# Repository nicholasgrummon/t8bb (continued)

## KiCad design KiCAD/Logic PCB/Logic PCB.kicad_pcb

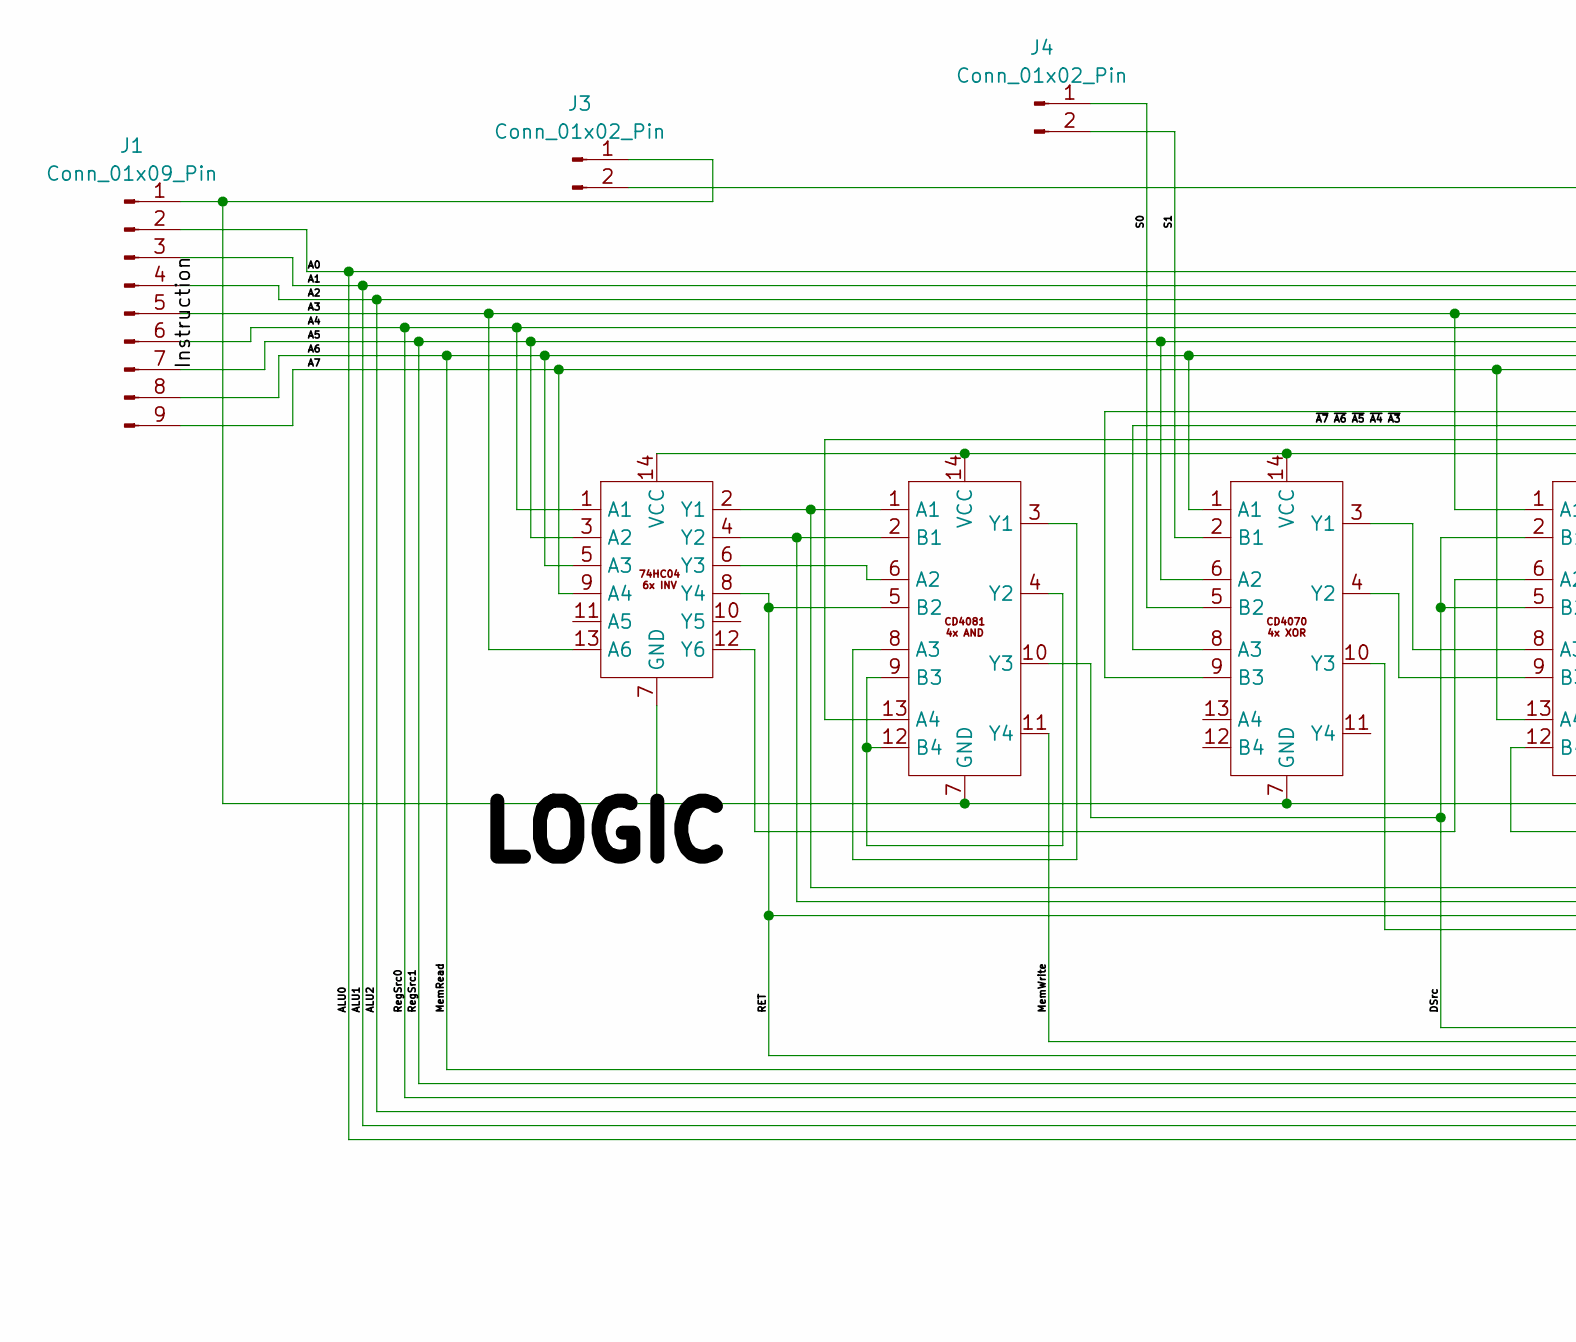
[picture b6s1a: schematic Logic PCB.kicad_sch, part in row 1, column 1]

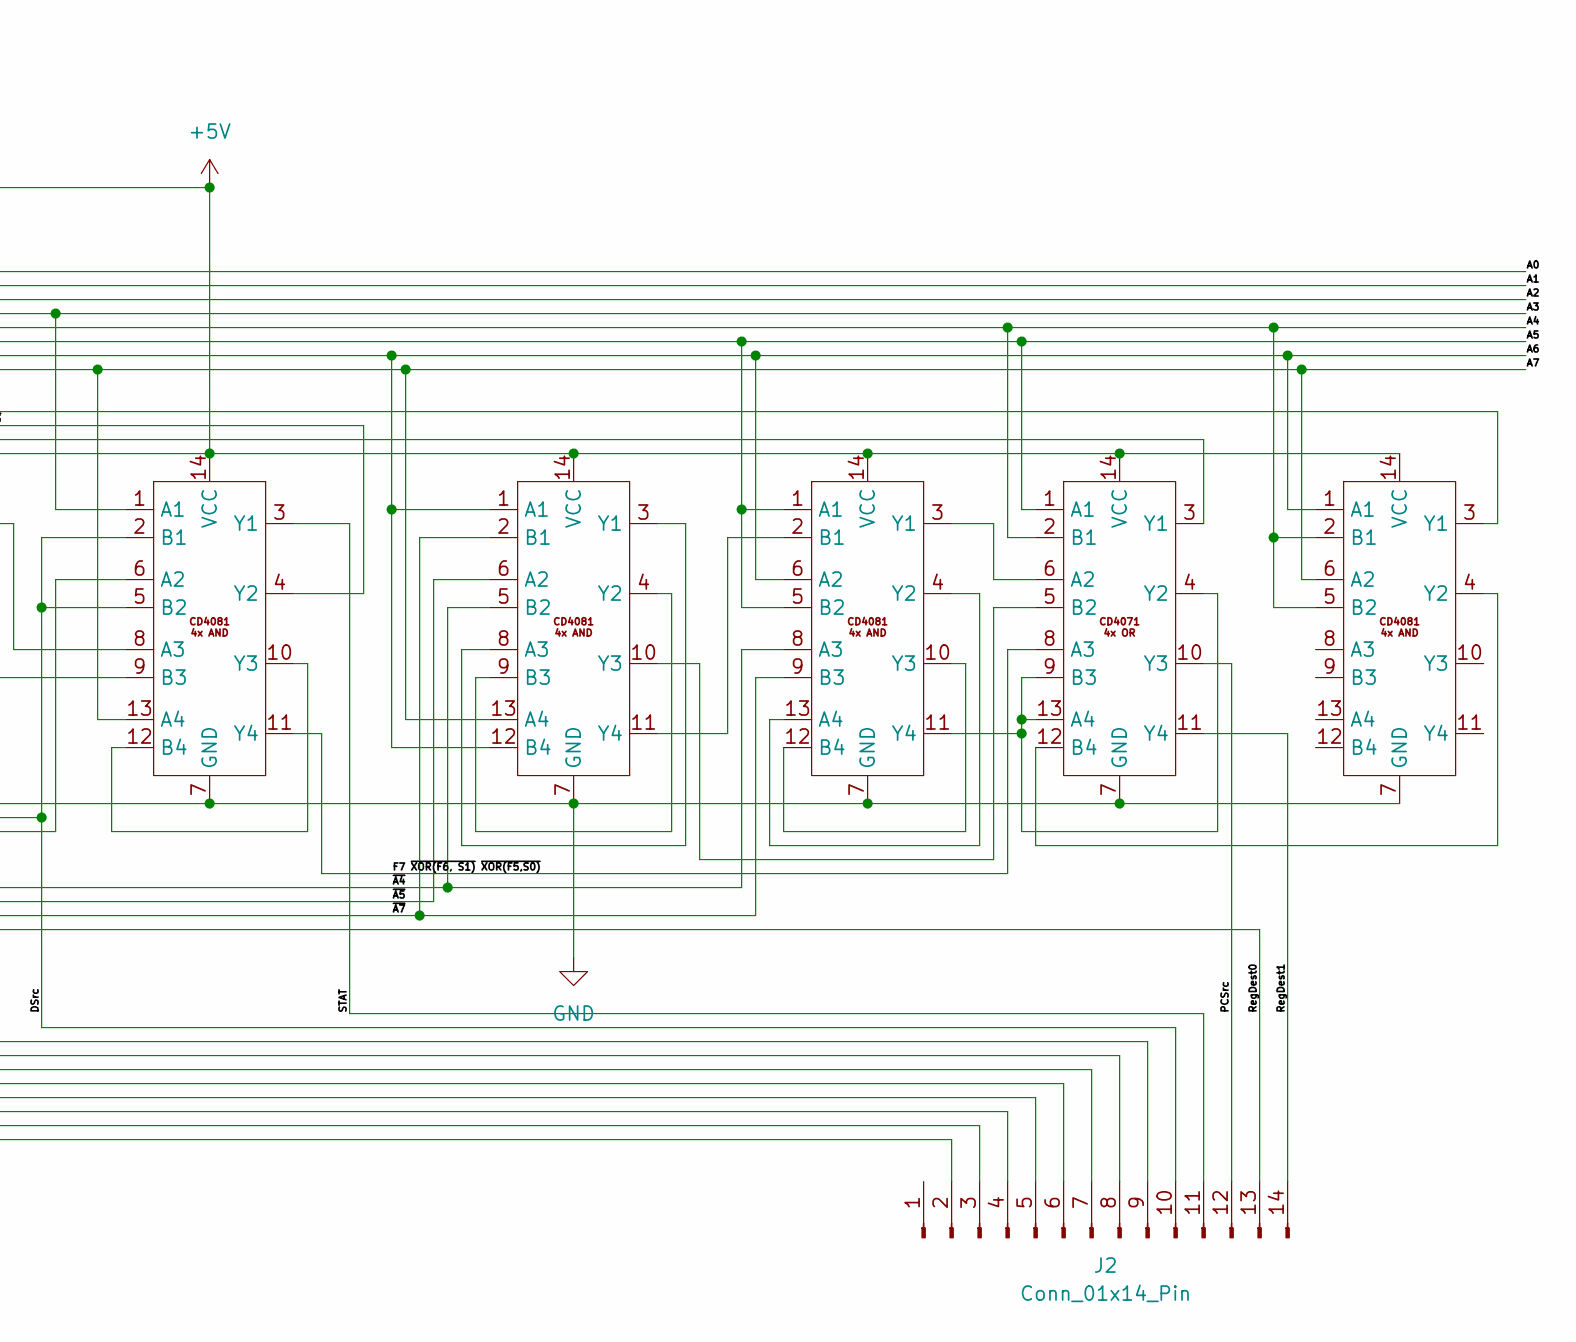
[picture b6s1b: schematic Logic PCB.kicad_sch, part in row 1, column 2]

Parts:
74HC1: 14pinbase; LCSC C507192
CD1, CD3, CD4, CD5, CD7: 14pinbase; LCSC C507156
CD2: 14pinbase; LCSC C30170096
CD6: 14pinbase; LCSC C3007968
J1: Conn_01x09_Pin; PinHeader_1x09_P2.54mm_Vertical
J2: Conn_01x14_Pin; PinHeader_1x14_P2.54mm_Vertical
J3, J4: Conn_01x02_Pin; PinHeader_1x02_P2.54mm_Vertical

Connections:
+5V: 74HC1.14 (VCC), CD1.14 (VCC), CD2.14 (VCC), CD3.14 (VCC), CD4.14 (VCC), CD5.14 (VCC), CD6.14 (VCC), CD7.14 (VCC), J3.2
/A0: J1.2, J2.2
/A1: J1.3, J2.3
/A2: J1.4, J2.4
/A3: 74HC1.13 (A6), CD3.1 (A1), J1.5
/A4: 74HC1.1 (A1), CD6.2 (B1), CD7.2 (B1), CD7.5 (B2), J1.6, J2.5
/A5: 74HC1.3 (A2), CD2.6 (A2), CD5.1 (A1), CD5.5 (B2), CD6.1 (A1), J1.7, J2.6
/A6: 74HC1.5 (A3), CD2.1 (A1), CD4.1 (A1), CD4.12 (B4), CD5.6 (A2), CD7.1 (A1), J1.8, J2.7
/A7: 74HC1.9 (A4), CD3.13 (A4), CD4.13 (A4), CD7.6 (A2), J1.9
/DSrc: CD1.10 (Y3), CD3.2 (B1), CD3.5 (B2), J2.10
/F7 ~XOR(F6, S1) ~XOR(F5,S0): CD3.11 (Y4), CD6.8 (A3)
/MemWrite: CD1.11 (Y4), J2.9
/PCSrc: CD6.10 (Y3), J2.12
/RET: 74HC1.8 (Y4), CD1.5 (B2), CD4.2 (B1), CD5.9 (B3), J2.8
/RegDest0: CD2.10 (Y3), J2.13
/RegDest1: CD6.11 (Y4), J2.14
/S0: CD2.5 (B2), J4.1
/S1: CD2.2 (B1), J4.2
/STAT: CD3.3 (Y1), J2.11
/~A4: 74HC1.2 (Y1), CD1.1 (A1), CD4.5 (B2), CD5.8 (A3)
/~A5: 74HC1.4 (Y2), CD1.2 (B1), CD4.6 (A2)
/~A7 ~A6 ~A5 ~A4 ~A3: CD2.8 (A3), CD3.4 (Y2)
GND: 74HC1.7 (GND), CD1.7 (GND), CD2.7 (GND), CD3.7 (GND), CD4.7 (GND), CD5.7 (GND), CD6.7 (GND), CD7.7 (GND), J1.1, J3.1
unnamed: 74HC1.6 (Y3), CD1.6 (A2)
unnamed: 74HC1.12 (Y6), CD3.6 (A2)
unnamed: CD1.3 (Y1), CD1.8 (A3)
unnamed: CD1.13 (A4), CD6.3 (Y1)
unnamed: CD1.4 (Y2), CD1.9 (B3), CD1.12 (B4)
unnamed: CD2.9 (B3), CD7.3 (Y1)
unnamed: CD2.3 (Y1), CD3.8 (A3)
unnamed: CD2.4 (Y2), CD3.9 (B3)
unnamed: CD3.10 (Y3), CD3.12 (B4)
unnamed: CD4.3 (Y1), CD4.8 (A3)
unnamed: CD4.4 (Y2), CD4.9 (B3)
unnamed: CD4.10 (Y3), CD6.5 (B2)
unnamed: CD4.11 (Y4), CD5.2 (B1)
unnamed: CD5.4 (Y2), CD5.13 (A4)
unnamed: CD5.10 (Y3), CD5.12 (B4)
unnamed: CD5.3 (Y1), CD6.6 (A2)
unnamed: CD5.11 (Y4), CD6.4 (Y2), CD6.9 (B3), CD6.13 (A4)
unnamed: CD6.12 (B4), CD7.4 (Y2)

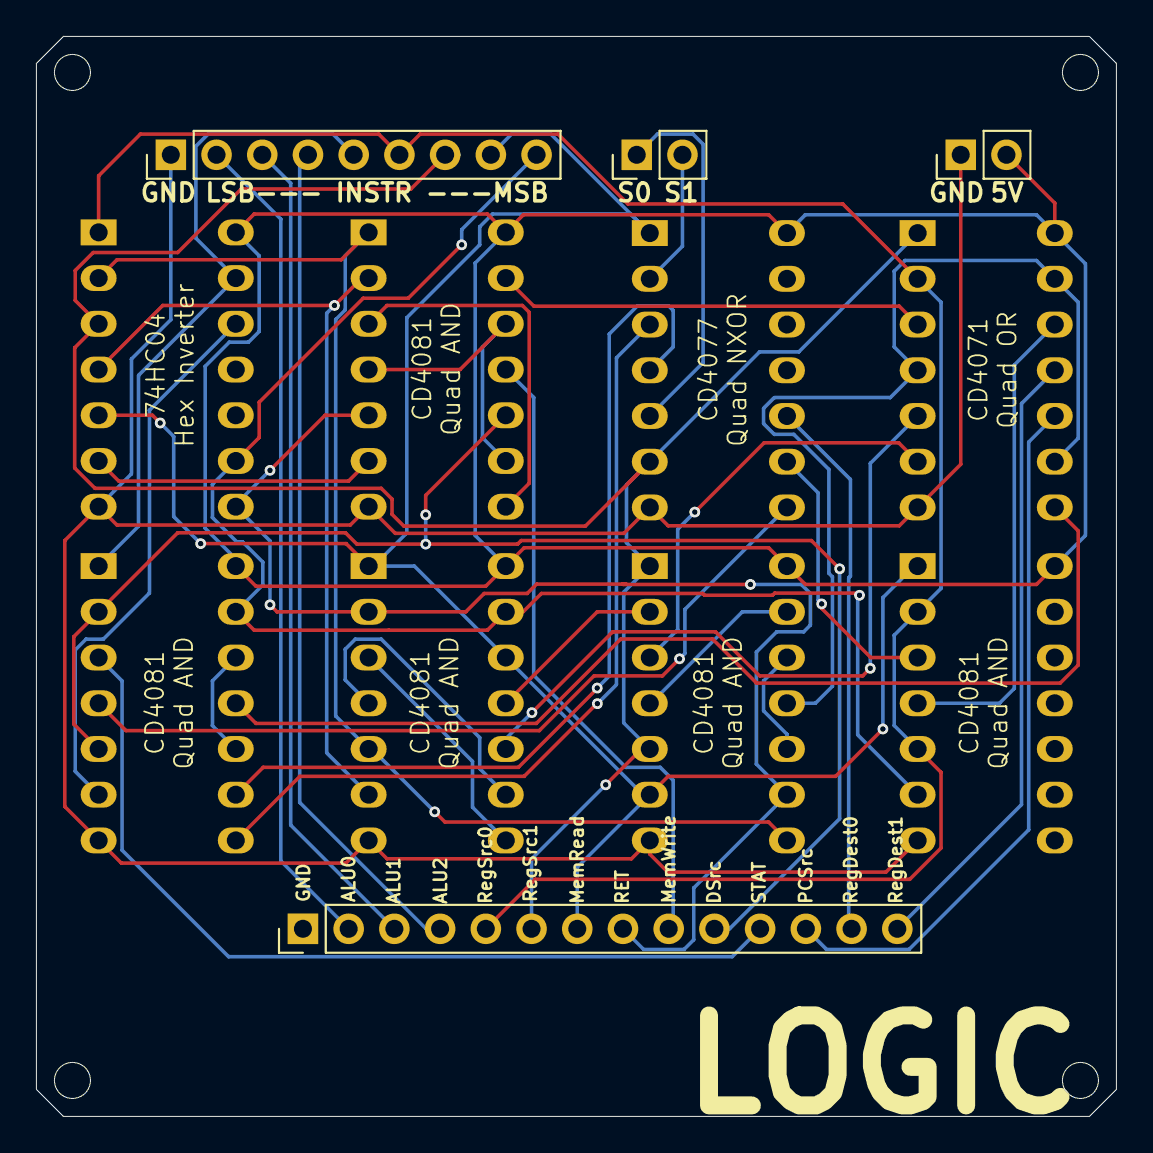
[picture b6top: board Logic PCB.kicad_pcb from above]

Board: 2 copper layers, 60.0 x 60.0 mm, 12 parts (0 on the bottom side), 41 nets.

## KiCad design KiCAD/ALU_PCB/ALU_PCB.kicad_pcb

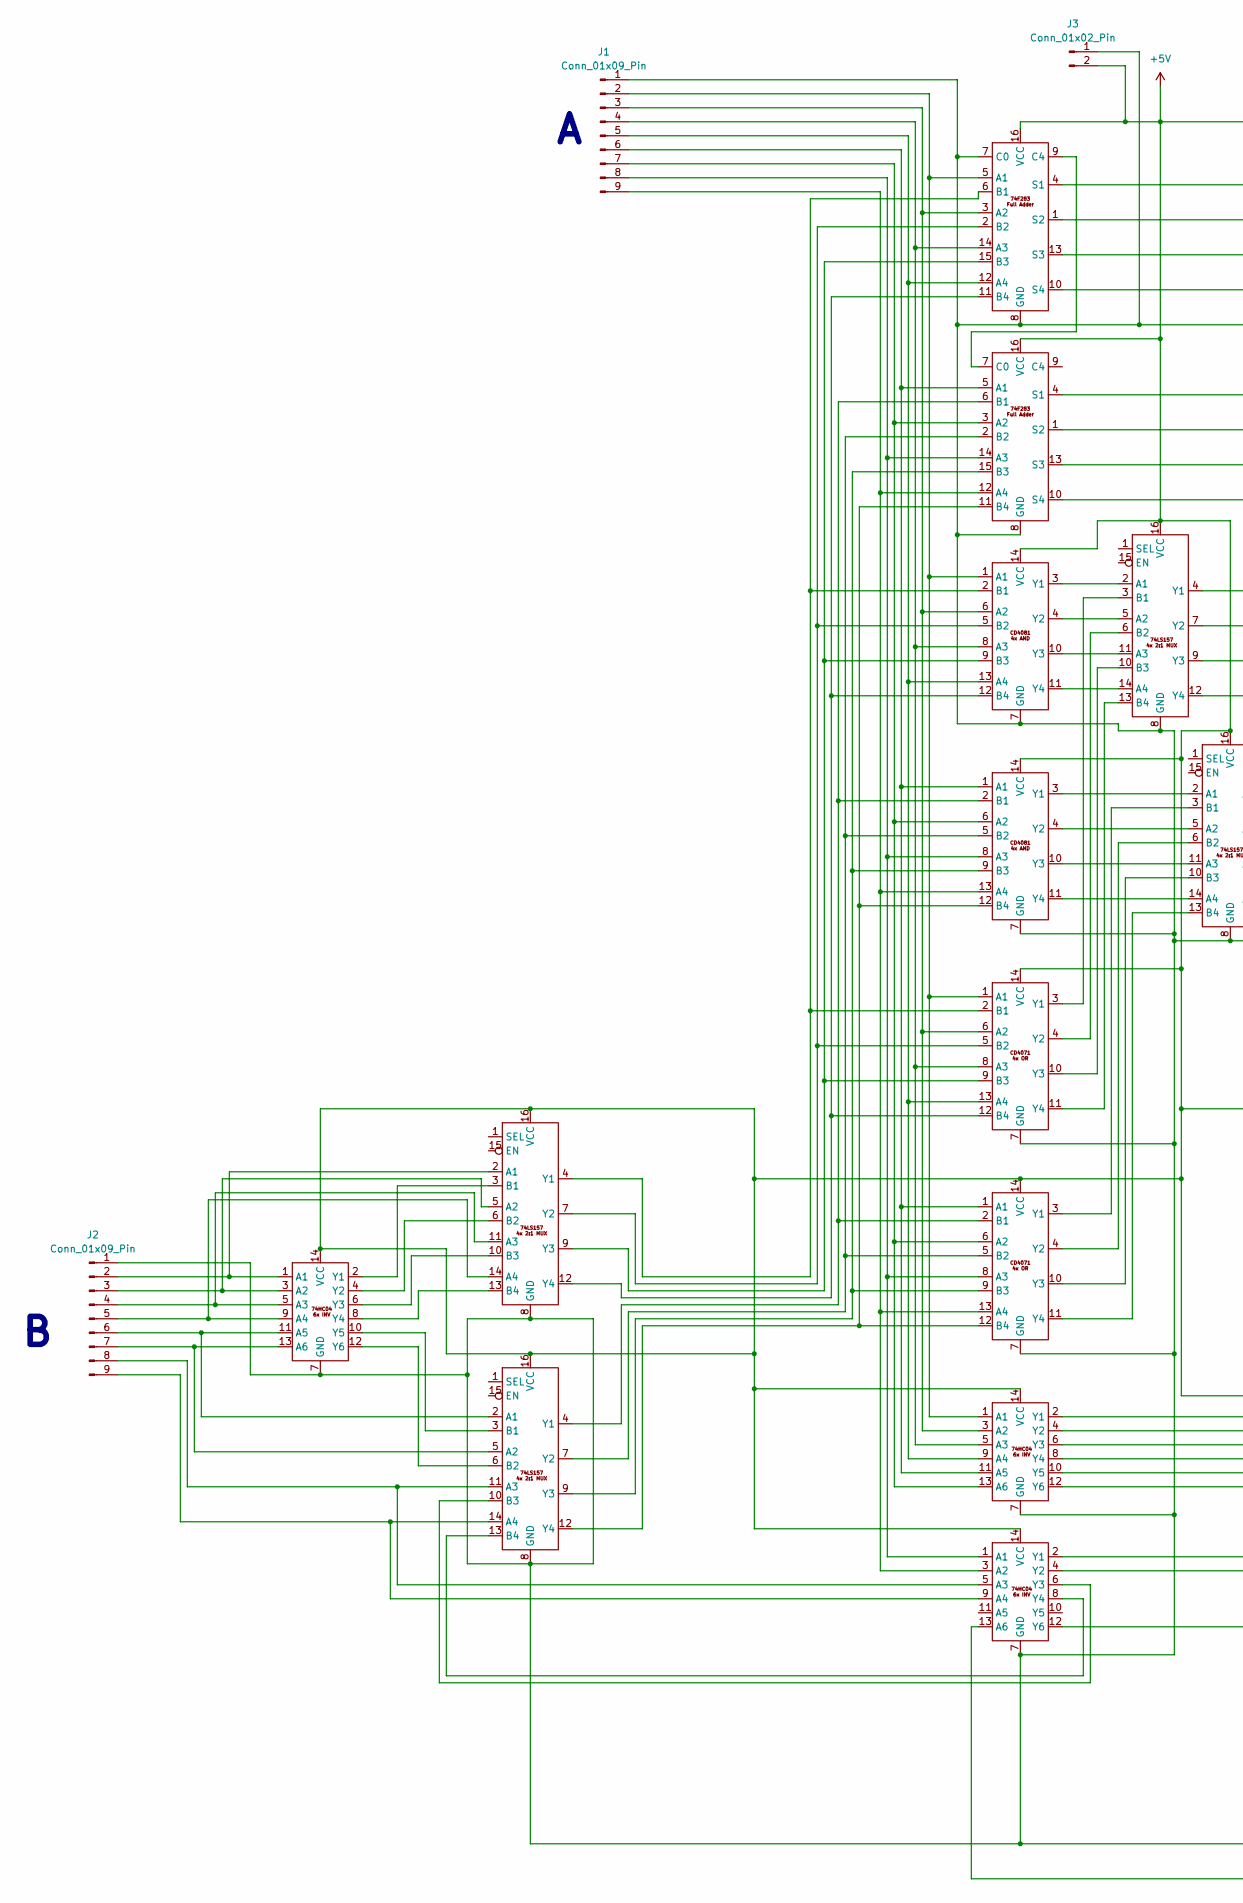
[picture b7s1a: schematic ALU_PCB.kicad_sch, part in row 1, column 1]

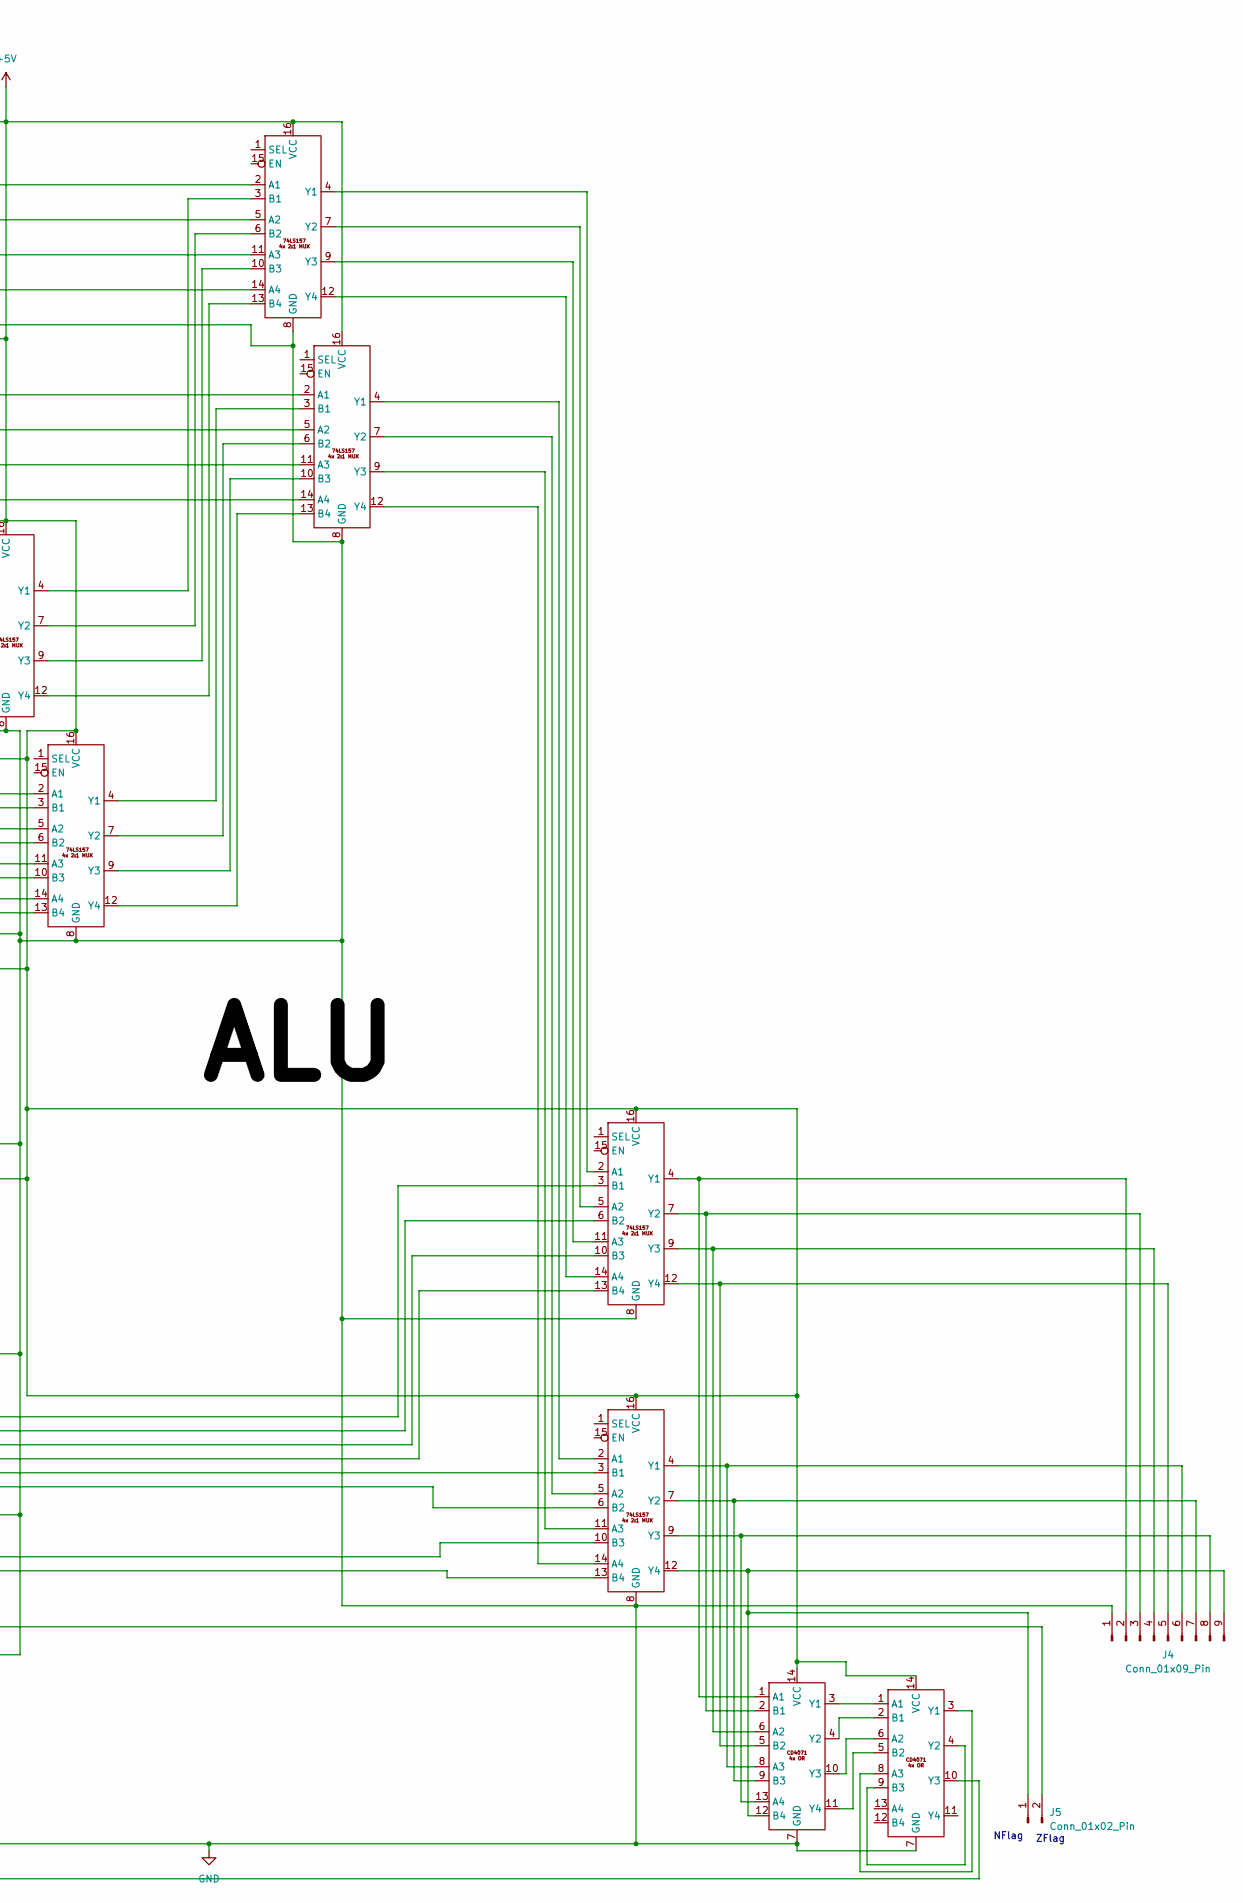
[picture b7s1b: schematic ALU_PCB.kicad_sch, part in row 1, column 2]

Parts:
74F1, 74F2, 74LS1, 74LS2, 74LS3, 74LS4, 74LS5, 74LS6, 74LS7, 74LS8: 16pinbase
74HC1, 74HC2, 74HC3: 14pinbase
CD1, CD2, CD3, CD4, CD5, CD6: 14pinbase
J1, J2, J4: Conn_01x09_Pin; PinHeader_1x09_P2.54mm_Vertical
J3, J5: Conn_01x02_Pin; PinHeader_1x02_P2.54mm_Vertical

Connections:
+5V: 74F1.16 (VCC), 74F2.16 (VCC), 74HC1.14 (VCC), 74HC2.14 (VCC), 74HC3.14 (VCC), 74LS1.16 (VCC), 74LS2.16 (VCC), 74LS3.16 (VCC), 74LS4.16 (VCC), 74LS5.16 (VCC), 74LS6.16 (VCC), 74LS7.16 (VCC), 74LS8.16 (VCC), CD1.14 (VCC), CD2.14 (VCC), CD3.14 (VCC), CD4.14 (VCC), CD5.14 (VCC), CD6.14 (VCC), J3.2
GND: 74F1.7 (C0), 74F1.8 (GND), 74F2.8 (GND), 74HC1.7 (GND), 74HC2.7 (GND), 74HC3.7 (GND), 74LS1.8 (GND), 74LS2.8 (GND), 74LS3.8 (GND), 74LS4.8 (GND), 74LS5.8 (GND), 74LS6.8 (GND), 74LS7.8 (GND), 74LS8.8 (GND), CD1.7 (GND), CD2.7 (GND), CD3.7 (GND), CD4.7 (GND), CD5.7 (GND), CD6.7 (GND), J1.1, J2.1, J3.1, J4.1
unnamed: 74F1.5 (A1), 74HC2.1 (A1), CD1.1 (A1), CD3.1 (A1), J1.2
unnamed: 74F1.3 (A2), 74HC2.3 (A2), CD1.6 (A2), CD3.6 (A2), J1.3
unnamed: 74F1.14 (A3), 74HC2.5 (A3), CD1.8 (A3), CD3.8 (A3), J1.4
unnamed: 74F1.12 (A4), 74HC2.9 (A4), CD1.13 (A4), CD3.13 (A4), J1.5
unnamed: 74F1.6 (B1), 74LS1.4 (Y1), CD1.2 (B1), CD3.2 (B1)
unnamed: 74F1.2 (B2), 74LS1.7 (Y2), CD1.5 (B2), CD3.5 (B2)
unnamed: 74F1.15 (B3), 74LS1.9 (Y3), CD1.9 (B3), CD3.9 (B3)
unnamed: 74F1.11 (B4), 74LS1.12 (Y4), CD1.12 (B4), CD3.12 (B4)
unnamed: 74F1.9 (C4), 74F2.7 (C0)
unnamed: 74F1.4 (S1), 74LS5.2 (A1)
unnamed: 74F1.1 (S2), 74LS5.5 (A2)
unnamed: 74F1.13 (S3), 74LS5.11 (A3)
unnamed: 74F1.10 (S4), 74LS5.14 (A4)
unnamed: 74F2.5 (A1), 74HC2.11 (A5), CD2.1 (A1), CD4.1 (A1), J1.6
unnamed: 74F2.3 (A2), 74HC2.13 (A6), CD2.6 (A2), CD4.6 (A2), J1.7
unnamed: 74F2.14 (A3), 74HC3.1 (A1), CD2.8 (A3), CD4.8 (A3), J1.8
unnamed: 74F2.12 (A4), 74HC3.3 (A2), CD2.13 (A4), CD4.13 (A4), J1.9
unnamed: 74F2.6 (B1), 74LS2.4 (Y1), CD2.2 (B1), CD4.2 (B1)
unnamed: 74F2.2 (B2), 74LS2.7 (Y2), CD2.5 (B2), CD4.5 (B2)
unnamed: 74F2.15 (B3), 74LS2.9 (Y3), CD2.9 (B3), CD4.9 (B3)
unnamed: 74F2.11 (B4), 74LS2.12 (Y4), CD2.12 (B4), CD4.12 (B4)
unnamed: 74F2.4 (S1), 74LS6.2 (A1)
unnamed: 74F2.1 (S2), 74LS6.5 (A2)
unnamed: 74F2.13 (S3), 74LS6.11 (A3)
unnamed: 74F2.10 (S4), 74LS6.14 (A4)
unnamed: 74HC1.1 (A1), 74LS1.2 (A1), J2.2
unnamed: 74HC1.3 (A2), 74LS1.5 (A2), J2.3
unnamed: 74HC1.5 (A3), 74LS1.11 (A3), J2.4
unnamed: 74HC1.9 (A4), 74LS1.14 (A4), J2.5
unnamed: 74HC1.11 (A5), 74LS2.2 (A1), J2.6
unnamed: 74HC1.13 (A6), 74LS2.5 (A2), J2.7
unnamed: 74HC1.2 (Y1), 74LS1.3 (B1)
unnamed: 74HC1.4 (Y2), 74LS1.6 (B2)
unnamed: 74HC1.6 (Y3), 74LS1.10 (B3)
unnamed: 74HC1.8 (Y4), 74LS1.13 (B4)
unnamed: 74HC1.10 (Y5), 74LS2.3 (B1)
unnamed: 74HC1.12 (Y6), 74LS2.6 (B2)
unnamed: 74HC2.2 (Y1), 74LS7.3 (B1)
unnamed: 74HC2.4 (Y2), 74LS7.6 (B2)
unnamed: 74HC2.6 (Y3), 74LS7.10 (B3)
unnamed: 74HC2.8 (Y4), 74LS7.13 (B4)
unnamed: 74HC2.10 (Y5), 74LS8.3 (B1)
unnamed: 74HC2.12 (Y6), 74LS8.6 (B2)
unnamed: 74HC3.5 (A3), 74LS2.11 (A3), J2.8
unnamed: 74HC3.9 (A4), 74LS2.14 (A4), J2.9
unnamed: 74HC3.13 (A6), CD6.10 (Y3)
unnamed: 74HC3.2 (Y1), 74LS8.10 (B3)
unnamed: 74HC3.4 (Y2), 74LS8.13 (B4)
unnamed: 74HC3.6 (Y3), 74LS2.10 (B3)
unnamed: 74HC3.8 (Y4), 74LS2.13 (B4)
unnamed: 74HC3.12 (Y6), J5.2
unnamed: 74LS3.2 (A1), CD1.3 (Y1)
unnamed: 74LS3.5 (A2), CD1.4 (Y2)
unnamed: 74LS3.11 (A3), CD1.10 (Y3)
unnamed: 74LS3.14 (A4), CD1.11 (Y4)
unnamed: 74LS3.3 (B1), CD3.3 (Y1)
unnamed: 74LS3.6 (B2), CD3.4 (Y2)
unnamed: 74LS3.10 (B3), CD3.10 (Y3)
unnamed: 74LS3.13 (B4), CD3.11 (Y4)
unnamed: 74LS3.4 (Y1), 74LS5.3 (B1)
unnamed: 74LS3.7 (Y2), 74LS5.6 (B2)
unnamed: 74LS3.9 (Y3), 74LS5.10 (B3)
unnamed: 74LS3.12 (Y4), 74LS5.13 (B4)
unnamed: 74LS4.2 (A1), CD2.3 (Y1)
unnamed: 74LS4.5 (A2), CD2.4 (Y2)
unnamed: 74LS4.11 (A3), CD2.10 (Y3)
unnamed: 74LS4.14 (A4), CD2.11 (Y4)
unnamed: 74LS4.3 (B1), CD4.3 (Y1)
unnamed: 74LS4.6 (B2), CD4.4 (Y2)
unnamed: 74LS4.10 (B3), CD4.10 (Y3)
unnamed: 74LS4.13 (B4), CD4.11 (Y4)
unnamed: 74LS4.4 (Y1), 74LS6.3 (B1)
unnamed: 74LS4.7 (Y2), 74LS6.6 (B2)
unnamed: 74LS4.9 (Y3), 74LS6.10 (B3)
unnamed: 74LS4.12 (Y4), 74LS6.13 (B4)
unnamed: 74LS5.4 (Y1), 74LS7.2 (A1)
unnamed: 74LS5.7 (Y2), 74LS7.5 (A2)
unnamed: 74LS5.9 (Y3), 74LS7.11 (A3)
unnamed: 74LS5.12 (Y4), 74LS7.14 (A4)
unnamed: 74LS6.4 (Y1), 74LS8.2 (A1)
unnamed: 74LS6.7 (Y2), 74LS8.5 (A2)
unnamed: 74LS6.9 (Y3), 74LS8.11 (A3)
unnamed: 74LS6.12 (Y4), 74LS8.14 (A4)
unnamed: 74LS7.4 (Y1), CD5.1 (A1), J4.2
unnamed: 74LS7.7 (Y2), CD5.2 (B1), J4.3
unnamed: 74LS7.9 (Y3), CD5.6 (A2), J4.4
unnamed: 74LS7.12 (Y4), CD5.5 (B2), J4.5
unnamed: 74LS8.4 (Y1), CD5.8 (A3), J4.6
unnamed: 74LS8.7 (Y2), CD5.9 (B3), J4.7
unnamed: 74LS8.9 (Y3), CD5.13 (A4), J4.8
unnamed: 74LS8.12 (Y4), CD5.12 (B4), J4.9, J5.1
unnamed: CD5.3 (Y1), CD6.1 (A1)
unnamed: CD5.4 (Y2), CD6.2 (B1)
unnamed: CD5.10 (Y3), CD6.6 (A2)
unnamed: CD5.11 (Y4), CD6.5 (B2)
unnamed: CD6.3 (Y1), CD6.8 (A3)
unnamed: CD6.4 (Y2), CD6.9 (B3)

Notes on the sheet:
NFlag
ZFlag

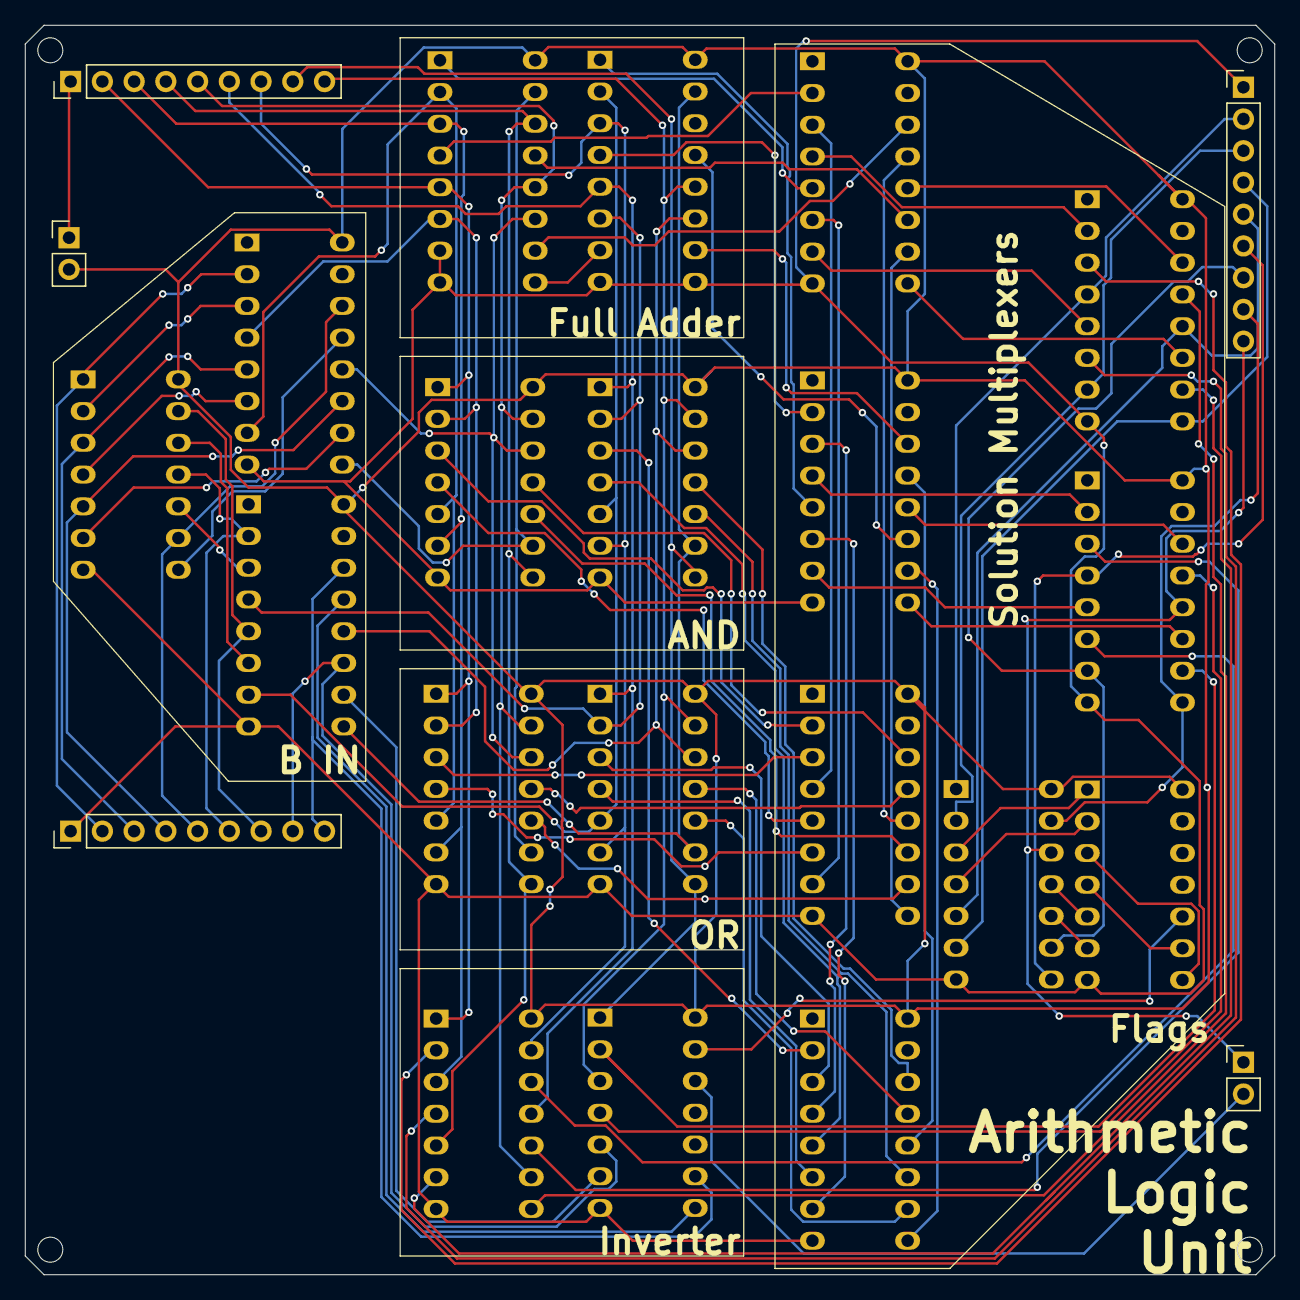
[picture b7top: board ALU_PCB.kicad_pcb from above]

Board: 2 copper layers, 100.0 x 100.0 mm, 24 parts (0 on the bottom side), 99 nets.

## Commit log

2026-06-02 Add README.md for KiCAD schematics and project history
    Document the history and challenges faced with the KiCAD project.
2026-06-02 Add base files
2026-06-02 Add stand-alone versions
2026-06-02 Add pictures
2026-06-02 Add demo video
2026-06-03 Remove demo video
